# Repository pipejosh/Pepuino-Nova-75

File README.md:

## Introducing the pepuino75

This is the pepuino75, a 75 percent keyboard, featuring my custom microcontroler, the pepuinoNanoV1 (https://github.com/pipejosh/pepuinoNano-devBoard) althought it is also compatible with a raspberry pi pico!. This keyboard also features a rotary encoder, design to make it as compact as possible, without lossing any of its features!

### Keyboard!

(With 3d printed display)

(With acrylic display)

### RENDER

### SCHEMATIC

### PCB
 
### CASE

### BOM

### Firmware

This keyboard uses kmk feel free to use the official (https://github.com/KMKfw/kmk_firmware/blob/main/docs/en/Getting_Started.md) documentation in order to flash and install kmk in you microcontroller the firmware folder has the code.py which is what you should copy and paste into your board 

## KIT Components

| Item | Description | Quantity | Unit Price | Total Price | URL |
|---|---|---:|---:|---:|---|
| Keycaps Set | Keycaps for the keyboard | 126 | 0.07 | 8.31 | https://www.aliexpress.com/item/1005007321700850.html |
| Switches | Mechanical switches | 90 | 0.20 | 18.11 | https://www.aliexpress.com/item/1005009787231480.html |
| Diodes | SMD diodes | 100 | 0.03 | 3.15 | https://www.aliexpress.com/item/1005007160563285.html |
| USB-C Cable | USB-C cable | 1 | 3.31 | 3.31 | https://www.aliexpress.com/item/1005005080440661.html |
| M2 Standoff | M2 standoff 5 mm | 50 | 0.05 | 2.50 | https://www.aliexpress.com/item/1005006049595637.html |
| M2 Screw | M2 screw 5 mm | 50 | 0.03 | 1.60 | https://www.aliexpress.com/item/1005005070119421.html |
| Stabilizers | MX stabilizers (6.25u & 2u) | 5 | 0.73 | 3.64 | https://www.aliexpress.com/item/1005007212869086.html |
| Taxes | AliExpress tax | — | — | 4.28 | — |

**KIT Components Subtotal:** 44.90

---

## PCB Costs

| Item | Description | Cost |
|---|---|---:|
| JLCPCB | Pepuino75 PCB | 26.47 |
| JLCPCB Shipping | PCB shipping + taxes | 21.58 |

**PCB Subtotal:** 48.05

---

## GRAND TOTAL

| Category | Amount |
|---|---:|
| KIT Components | 44.90 |
| PCB | 48.05 |
| **TOTAL** | **92.95** |

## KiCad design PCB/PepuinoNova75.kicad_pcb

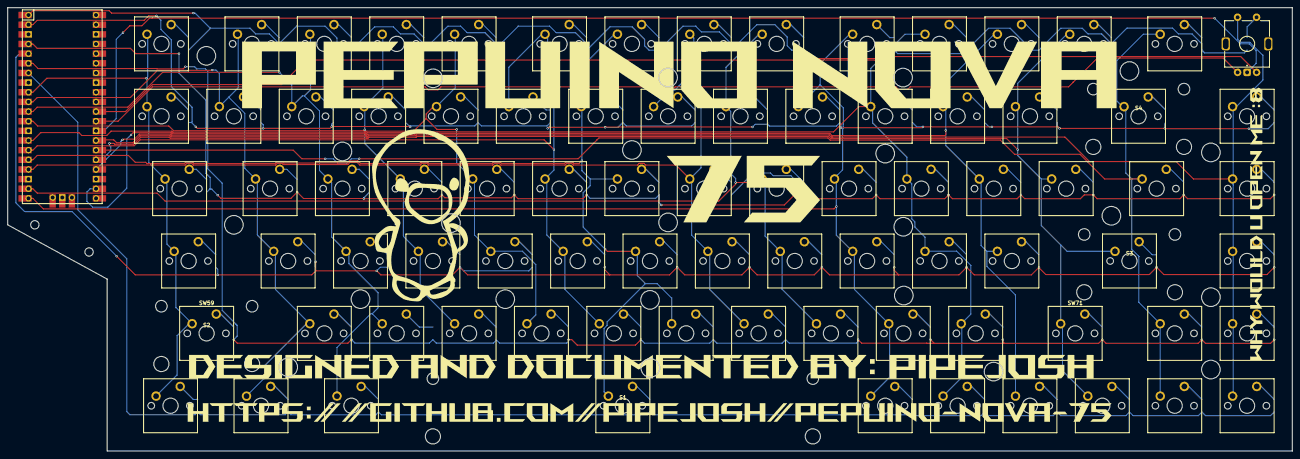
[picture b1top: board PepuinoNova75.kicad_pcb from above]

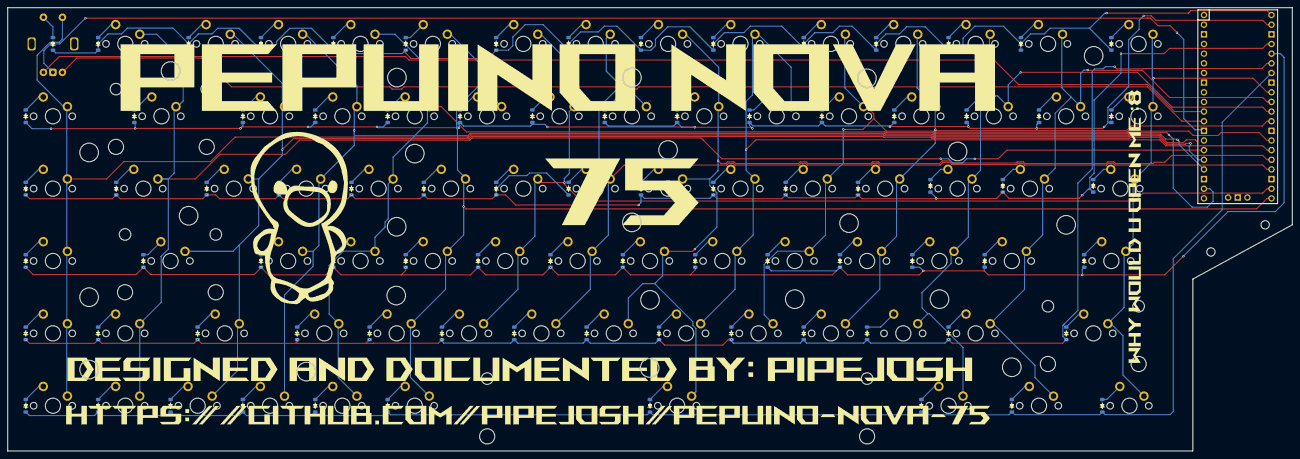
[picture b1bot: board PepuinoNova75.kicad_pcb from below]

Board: 2 copper layers, 338.1 x 116.7 mm, 173 parts (83 on the bottom side), 107 nets.

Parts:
D1, D2, D3, D4, D5, D6, D7, D8, D9, D10, D11, D12, D13, D14, D15, D16, D17, D18, D19, D20, D21, D22, D23, D24, D25, D26, D27, D28, D29, D30, D31, D32, D33, D34, D35, D36, D37, D38, D39, D40, D41, D42, D43, D44, D45, D46, D47, D48, D49, D50, D51, D52, D53, D54, D55, D56, D57, D58, D59, D60, D61, D62, D63, D64, D65, D66, D67, D68, D69, D71, D72, D73, D74, D75, D76, D77, D78, D79, D80, D81, D82, D83, D84: Diode_SOD-123
H16, H21: MountingHole; MountingHole_2.2mm_M2
S1: MX_stab; Stabilizer_MX_6.25u
S2, S3, S4: MX_stab; Stabilizer_MX_2.00u
SW1, SW2, SW3, SW4, SW5, SW6, SW7, SW8, SW9, SW10, SW11, SW12, SW13, SW14, SW15, SW16, SW17, SW18, SW19, SW20, SW21, SW22, SW23, SW24, SW25, SW26, SW27, SW29, SW31, SW32, SW33, SW34, SW35, SW36, SW37, SW38, SW39, SW40, SW41, SW42, SW44, SW46, SW47, SW48, SW49, SW50, SW51, SW52, SW53, SW54, SW55, SW56, SW58, SW60, SW61, SW62, SW63, SW64, SW65, SW66, SW67, SW68, SW69, SW72, SW77, SW78, SW79, SW80, SW81, SW82, SW84: Switch; MX_PCB_1.00u
SW28: Switch; MX_PCB_2.00u
SW30, SW43: Switch; MX_PCB_1.50u
SW45, SW71: Switch; MX_PCB_1.75u
SW57, SW59: Switch; MX_PCB_2.25u
SW73, SW74, SW75: Switch; MX_PCB_1.25u
SW76: Switch; MX_PCB_6.25u
SW83: RotaryEncoder_Switch; ROT_Alps_EC11E-Switch
U1: Raspberry_Pi_Pico

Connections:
COL0: SW1.1, SW15.1, SW30.1, SW45.1, SW59.1, SW73.1, U1.9 (GPIO6)
COL1: SW2.1, SW16.1, SW31.1, SW46.1, SW60.1, SW74.1, U1.10 (GPIO7)
COL2: SW3.1, SW17.1, SW32.1, SW47.1, SW61.1, SW75.1, U1.11 (GPIO8)
COL3: SW4.1, SW18.1, SW33.1, SW48.1, SW62.1, U1.12 (GPIO9)
COL4: SW5.1, SW19.1, SW34.1, SW49.1, SW63.1, U1.14 (GPIO10)
COL5: SW6.1, SW20.1, SW35.1, SW50.1, SW64.1, U1.15 (GPIO11)
COL6: SW7.1, SW21.1, SW36.1, SW51.1, SW65.1, SW76.1, U1.16 (GPIO12)
COL7: SW8.1, SW22.1, SW37.1, SW52.1, SW66.1, U1.17 (GPIO13)
COL8: SW9.1, SW23.1, SW38.1, SW53.1, SW67.1, U1.19 (GPIO14)
COL9: SW10.1, SW24.1, SW39.1, SW54.1, SW68.1, SW77.1, U1.20 (GPIO15)
COL10: SW11.1, SW25.1, SW40.1, SW55.1, SW69.1, SW78.1, U1.22 (GPIO17)
COL11: SW12.1, SW26.1, SW41.1, SW56.1, SW79.1, U1.24 (GPIO18)
COL12: SW13.1, SW27.1, SW42.1, SW57.1, SW71.1, SW80.1, U1.25 (GPIO19)
COL13: SW14.1, SW28.1, SW43.1, SW72.1, SW81.1, U1.26 (GPIO20)
COL14: SW29.1, SW44.1, SW58.1, SW82.1, SW83.S2, SW84.1, U1.27 (GPIO21)
GND: SW83.C, U1.28 (GND)
unnamed: D1.2 (A), SW1.2
unnamed: D2.2 (A), SW2.2
unnamed: D3.2 (A), SW3.2
unnamed: D4.2 (A), SW4.2
unnamed: D5.2 (A), SW5.2
unnamed: D6.2 (A), SW6.2
unnamed: D7.2 (A), SW7.2
unnamed: D8.2 (A), SW8.2
unnamed: D9.2 (A), SW9.2
unnamed: D10.2 (A), SW10.2
unnamed: D11.2 (A), SW11.2
unnamed: D12.2 (A), SW12.2
unnamed: D13.2 (A), SW13.2
unnamed: D14.2 (A), SW14.2
unnamed: D15.2 (A), SW15.2
unnamed: D16.2 (A), SW16.2
unnamed: D17.2 (A), SW17.2
unnamed: D18.2 (A), SW18.2
unnamed: D19.2 (A), SW19.2
unnamed: D20.2 (A), SW20.2
unnamed: D21.2 (A), SW21.2
unnamed: D22.2 (A), SW22.2
unnamed: D23.2 (A), SW23.2
unnamed: D24.2 (A), SW24.2
unnamed: D25.2 (A), SW25.2
unnamed: D26.2 (A), SW26.2
unnamed: D27.2 (A), SW27.2
unnamed: D28.2 (A), SW28.2
unnamed: D29.2 (A), SW29.2
unnamed: D30.2 (A), SW30.2
unnamed: D31.2 (A), SW31.2
unnamed: D32.2 (A), SW32.2
unnamed: D33.2 (A), SW33.2
unnamed: D34.2 (A), SW34.2
unnamed: D35.2 (A), SW35.2
unnamed: D36.2 (A), SW36.2
unnamed: D37.2 (A), SW37.2
unnamed: D38.2 (A), SW38.2
unnamed: D39.2 (A), SW39.2
unnamed: D40.2 (A), SW40.2
unnamed: D41.2 (A), SW41.2
unnamed: D42.2 (A), SW42.2
unnamed: D43.2 (A), SW43.2
unnamed: D44.2 (A), SW44.2
unnamed: D45.2 (A), SW45.2
unnamed: D46.2 (A), SW46.2
unnamed: D47.2 (A), SW47.2
unnamed: D48.2 (A), SW48.2
unnamed: D49.2 (A), SW49.2
unnamed: D50.2 (A), SW50.2
unnamed: D51.2 (A), SW51.2
unnamed: D52.2 (A), SW52.2
unnamed: D53.2 (A), SW53.2
unnamed: D54.2 (A), SW54.2
unnamed: D55.2 (A), SW55.2
unnamed: D56.2 (A), SW56.2
unnamed: D57.2 (A), SW57.2
unnamed: D58.2 (A), SW58.2
unnamed: D59.2 (A), SW59.2
unnamed: D60.2 (A), SW60.2
unnamed: D61.2 (A), SW61.2
unnamed: D62.2 (A), SW62.2
unnamed: D63.2 (A), SW63.2
unnamed: D64.2 (A), SW64.2
unnamed: D65.2 (A), SW65.2
unnamed: D66.2 (A), SW66.2
unnamed: D67.2 (A), SW67.2
unnamed: D68.2 (A), SW68.2
unnamed: D69.2 (A), SW69.2
unnamed: D71.2 (A), SW71.2
unnamed: D72.2 (A), SW72.2
unnamed: D73.2 (A), SW73.2
unnamed: D74.2 (A), SW74.2
unnamed: D75.2 (A), SW75.2
unnamed: D76.2 (A), SW76.2
unnamed: D77.2 (A), SW77.2
unnamed: D78.2 (A), SW78.2
unnamed: D79.2 (A), SW79.2
unnamed: D80.2 (A), SW80.2
unnamed: D81.2 (A), SW81.2
unnamed: D82.2 (A), SW82.2
unnamed: D83.2 (A), SW83.S1
unnamed: D84.2 (A), SW84.2
ROW0: D1.1 (K), D2.1 (K), D3.1 (K), D4.1 (K), D5.1 (K), D6.1 (K), D7.1 (K), D8.1 (K), D9.1 (K), D10.1 (K), D11.1 (K), D12.1 (K), D13.1 (K), D14.1 (K), D83.1 (K), U1.1 (GPIO0)
ROW1: D15.1 (K), D16.1 (K), D17.1 (K), D18.1 (K), D19.1 (K), D20.1 (K), D21.1 (K), D22.1 (K), D23.1 (K), D24.1 (K), D25.1 (K), D26.1 (K), D27.1 (K), D28.1 (K), D29.1 (K), U1.2 (GPIO1)
ROW2: D30.1 (K), D31.1 (K), D32.1 (K), D33.1 (K), D34.1 (K), D35.1 (K), D36.1 (K), D37.1 (K), D38.1 (K), D39.1 (K), D40.1 (K), D41.1 (K), D42.1 (K), D43.1 (K), D44.1 (K), U1.4 (GPIO2)
ROW3: D45.1 (K), D46.1 (K), D47.1 (K), D48.1 (K), D49.1 (K), D50.1 (K), D51.1 (K), D52.1 (K), D53.1 (K), D54.1 (K), D55.1 (K), D56.1 (K), D57.1 (K), D58.1 (K), U1.5 (GPIO3)
ROW4: D59.1 (K), D60.1 (K), D61.1 (K), D62.1 (K), D63.1 (K), D64.1 (K), D65.1 (K), D66.1 (K), D67.1 (K), D68.1 (K), D69.1 (K), D71.1 (K), D72.1 (K), D84.1 (K), U1.6 (GPIO4)
ROW5: D73.1 (K), D74.1 (K), D75.1 (K), D76.1 (K), D77.1 (K), D78.1 (K), D79.1 (K), D80.1 (K), D81.1 (K), D82.1 (K), U1.7 (GPIO5)
rotaryA: SW83.A, U1.29 (GPIO22)
rotaryB: SW83.B, U1.30 (RUN)

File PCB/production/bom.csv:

Designator,Footprint,Quantity,Value,LCSC Part #
"D1, D10, D11, D12, D13, D14, D15, D16, D17, D18, D19, D2, D20, D21, D22, D23, D24, D25, D26, D27, D28, D29, D3, D30, D31, D32, D33, D34, D35, D36, D37, D38, D39, D4, D40, D41, D42, D43, D44, D45, D46, D47, D48, D49, D5, D50, D51, D52, D53, D54, D55, D56, D57, D58, D59, D6, D60, D61, D62, D63, D64, D65, D66, D67, D68, D69, D7, D71, D72, D73, D74, D75, D76, D77, D78, D79, D8, D80, D81, D82, D83, D84, D9",Diode_SOD-123,83,~,
S1,Stabilizer_MX_6.25u,1,MX_stab,
"S2, S3, S4, S5",Stabilizer_MX_2.00u,4,MX_stab,
"SW1, SW10, SW11, SW12, SW13, SW14, SW15, SW16, SW17, SW18, SW19, SW2, SW20, SW21, SW22, SW23, SW24, SW25, SW26, SW27, SW29, SW3, SW31, SW32, SW33, SW34, SW35, SW36, SW37, SW38, SW39, SW4, SW40, SW41, SW42, SW44, SW46, SW47, SW48, SW49, SW5, SW50, SW51, SW52, SW53, SW54, SW55, SW56, SW58, SW6, SW60, SW61, SW62, SW63, SW64, SW65, SW66, SW67, SW68, SW69, SW7, SW72, SW77, SW78, SW79, SW8, SW80, SW81, SW82, SW84, SW9",MX_PCB_1.00u,71,Switch,
SW28,MX_PCB_2.00u,1,Switch,
"SW30, SW43",MX_PCB_1.50u,2,Switch,
"SW45, SW71",MX_PCB_1.75u,2,Switch,
"SW57, SW59",MX_PCB_2.25u,2,Switch,
"SW73, SW74, SW75",MX_PCB_1.25u,3,Switch,
SW76,MX_PCB_6.25u,1,Switch,
SW83,ROT_Alps_EC11E-Switch,1,RotaryEncoder_Switch,
U1,Raspberry_Pi_Pico,1,Raspberry_Pi_Pico,

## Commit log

2026-03-19 update images and add silkscreen pcb
2026-03-27 Update CAD files
2026-03-27 update pcb and fix crucial mistakes
2026-03-27 add kmk firmware
2026-03-27 add irl picture of the keb
2026-03-27 update pictures
2026-03-27 Reintroduce pepuino75 project details in README
2026-03-28 Revise README to enhance keyboard introduction and details
2026-04-01 fix fatal error in pcb + fix case + update images
2026-04-01 update rotary encoder firmware
2026-04-01 update documentation on the firmware
2026-04-01 fix spelling and add kmk getting started link
2026-04-01 add journal!!!!!!!!
2026-04-10 add the acrylic piece dxf (in mm)
2026-04-10 add new picture with the acrylic
2026-04-10 Enhance README with new images and details
    Updated the README to include additional images and improved descriptions for the pepuino75 keyboard.
2026-04-10 updadte jourrnal
